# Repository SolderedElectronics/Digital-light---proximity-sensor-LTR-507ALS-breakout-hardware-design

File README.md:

# Digital light & proximity sensor LTR-507 breakout Hardware Design

## About the Product

|  |
| :----------------------------------------------------------: |
| [Buy Digital light & proximity sensor LTR-507 breakout](https://www.solde.red/333063) |

For very precise measurements of the amount of light, take this digital light sensor into account (ALS – Ambient Light Sensor). In addition, the LTR-507ALS also measures the proximity (PS – Proximity Sensor) of the object to the sensor. It sends all this data via I2C communication, which is easy to read via our Arduino library.

---

## Repository Contents

This repository contains all design files for Digital light & proximity sensor LTR-507 breakout, organized as follows:

- **`CAD` folder**: Contains KiCAD design files, including:
  - Schematics
  - PCB layout
  - Panel PCB layout
  - Source 3D files in Fusion360, if any
  - All files are sorted by version with a detailed change log.
- **`OUTPUTS` folder**: Includes all production-ready files, such as:
  - Bill of Materials (BOM) and interactive BOM (iBOM)
  - PDF versions of schematics
  - 3D `.step` file of the board
  - 3D-printable models
  - Gerber files for PCB manufacturing
  - Image of the pinout of the board
  - Product image
  - Compliance, legal and generic sales documents

Refer to the `Change Log` in the CAD folder for details about updates between versions.

---

## Learn More About the Product

Beyond the repository, explore the following resources:

### Soldered Verify

The **Soldered Verify** system ensures every board you purchase from Soldered is fully functional. It also provides access to exclusive test data for your product. To get started, find the unique Soldered Verify ID on your product's packaging and enter the ID on the [Soldered Verify page](https://soldered.com/verify/) to access test results and additional product details.

### Soldered Community

Soldered Community is your go-to place for technical support. Our engineers track and answer all questions posted there, and it’s a great space for the maker community. Get answers to your questions and solutions for your challenges at [Soldered Community](https://soldered.com/community).

### solde.red

solde.red is an ultimate URL shortener and information hub. Access it by typing solde.red/ followed by your product SKU, e.g., [solde.red/333000](https://solde.red/333000), to find getting-started guides, datasheets, open-source hardware and software files, certifications, images, pinouts, and more. Read more about the shortener [here](https://solde.red/info/).

---

## Contributing

Contributions are welcome! Here’s how you can get involved:

- Submit pull requests to enhance the design or fix issues.
- Report bugs or problems by opening an issue.

We encourage community collaboration to make this product even better.

---

## About Soldered

[Soldered for Makers](https://soldered.com) specializes in designing and manufacturing electronic products tailored for enthusiasts, ranging from hobbyists to professionals. Our portfolio includes electronic boards, sensors, and actuators that are widely utilized in fields such as microelectronics, mechatronics, robotics, programming, and IoT. Every product we offer is designed in-house and built upon open-source hardware and software platforms. Proudly certified and manufactured within the European Union, our catalog likely includes the product you need for your project.

We complement these products with comprehensive tutorials and manuals, product descriptions, schematics, programming codes, and project examples. Our round-the-clock [customer and technical support](https://soldered.com/community) is available for all our products, irrespective of the sales channel. Soldered’s success and services reflect our maker community’s unwavering [trust](https://www.trustpilot.com/review/soldered.com), for which we are deeply grateful. Join our community and create using Soldered products.

---

## License

All Soldered open-source hardware (OSH) is under The TAPR Open Hardware License. Read more in the LICENSE file located in this repository.

**Disclaimer:**

No warranty - all designs in this repository are distributed in the hope that they will be useful, but without any warranty. They are provided "AS IS", therefore without warranty of any kind, either expressed or implied. The entire quality and performance of what you do with the contents of this repository are your responsibility. In no event Soldered Electronics will be liable for your damages, or losses, including any general, special, incidental, or consequential damage arising out of the use or inability to use the contents of this repository. 

---

## Have fun!

Thank you for your support from your fellow makers at Soldered Electronics.

Happy Making!

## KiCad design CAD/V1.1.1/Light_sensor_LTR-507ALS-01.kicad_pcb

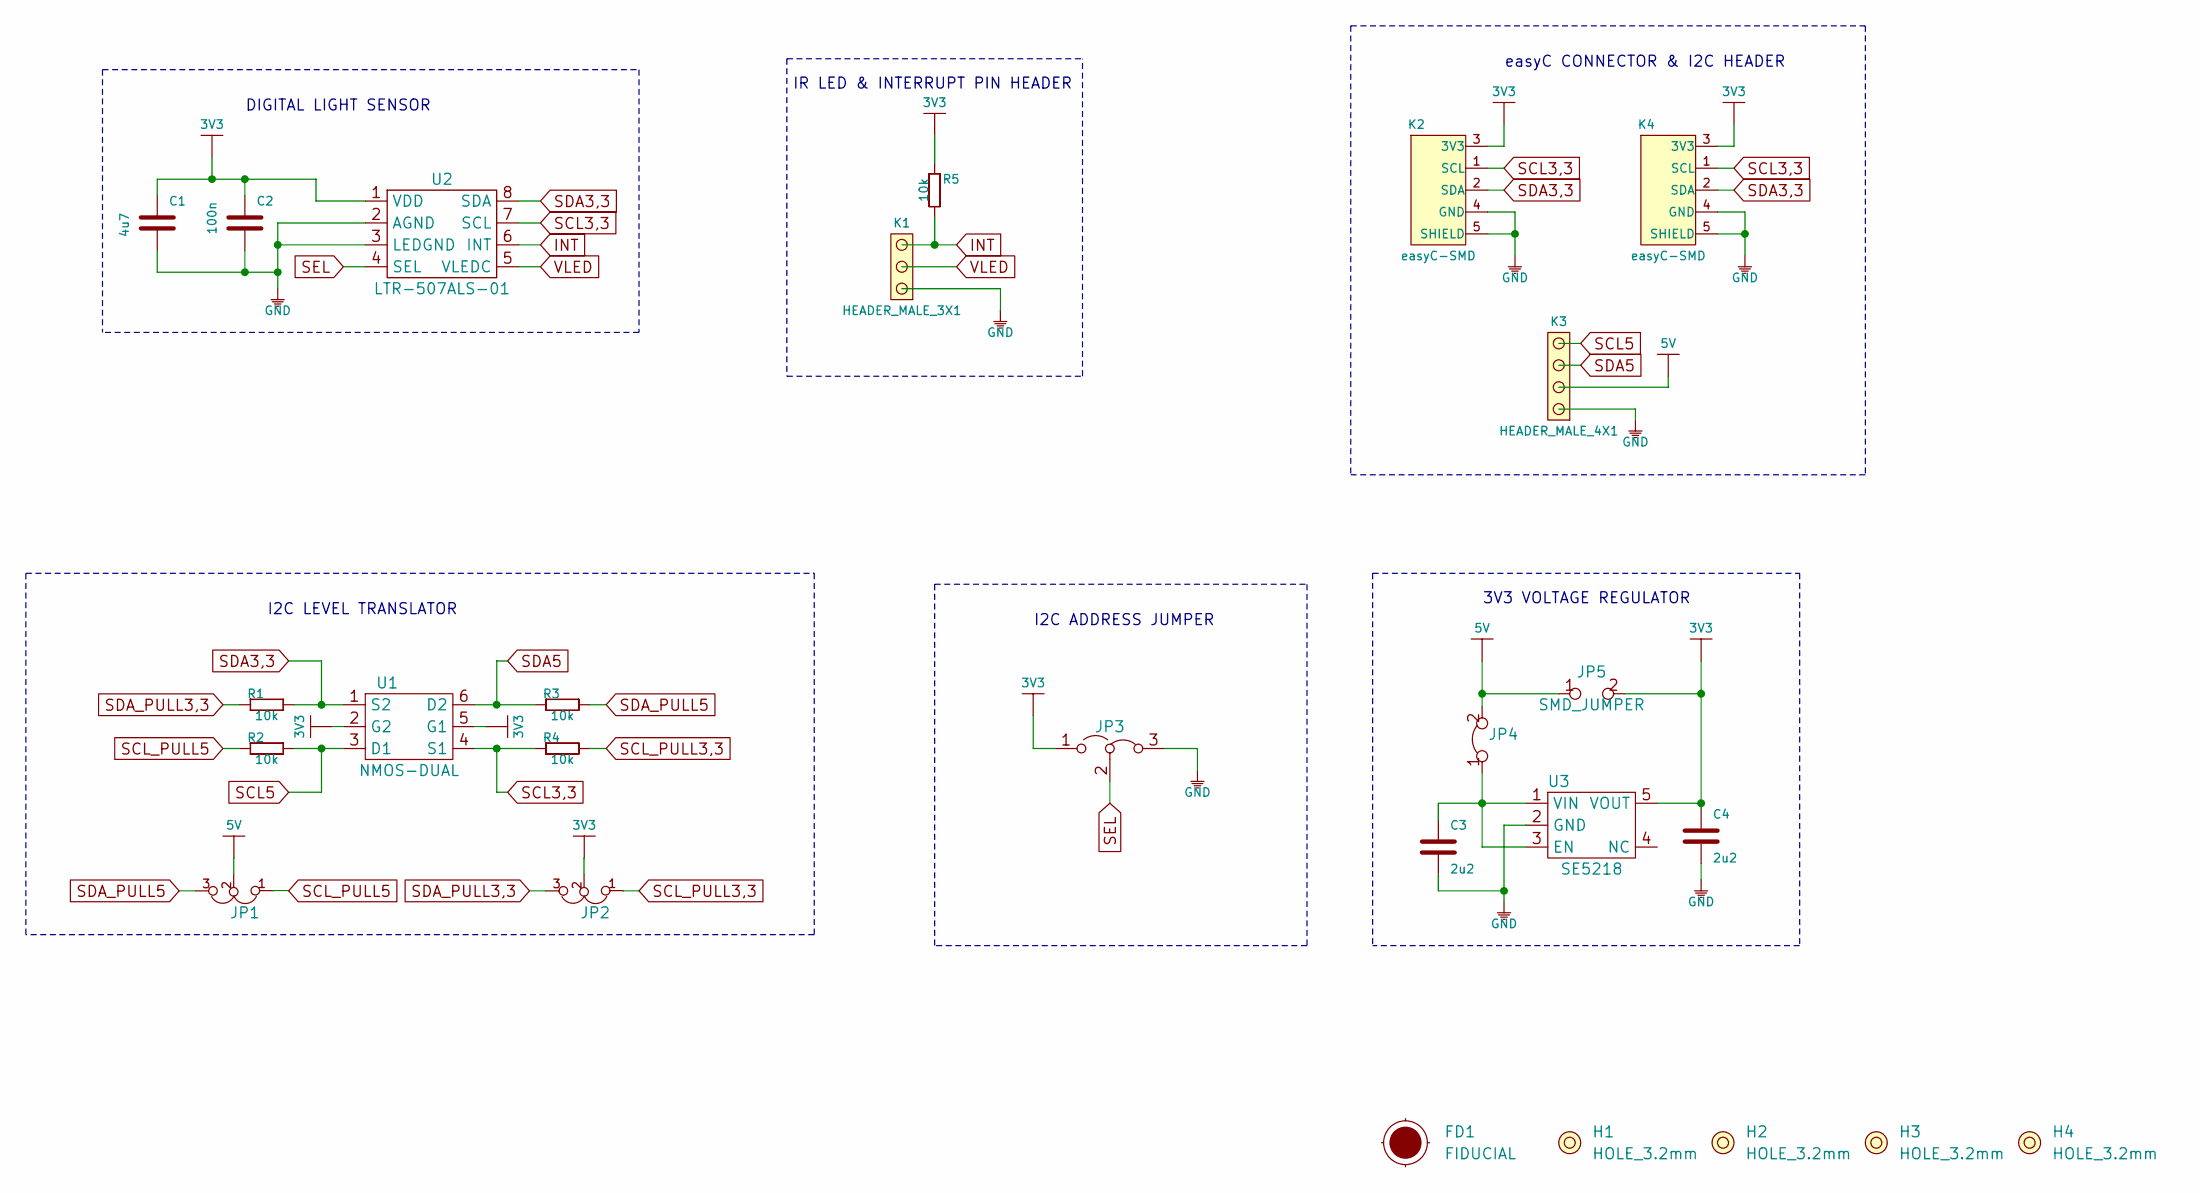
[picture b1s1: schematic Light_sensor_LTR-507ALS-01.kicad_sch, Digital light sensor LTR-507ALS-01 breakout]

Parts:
C1: 4u7; 0603C
C2: 100n; 0603C
C3, C4: 2u2; 0603C
FD1: FIDUCIAL; FIDUCIAL_23
H1, H2, H3, H4: HOLE_3.2mm
JP1, JP2: SMD_JUMPER_3_PAD_TRACE
JP3: JUMPER_3_RIGHT; SMD_JUMPER_3_PAD_CONNECTED_RIGHT
JP4: SMD-JUMPER-CONNECTED_TRACE_SLODERMASK
JP5: SMD_JUMPER
K1: HEADER_MALE_3X1
K2, K4: easyC-SMD; easyC-connector
K3: HEADER_MALE_4X1
R1, R2, R3, R4, R5: 10k; 0603R
U1: NMOS-DUAL; SOT-363
U2: LTR-507ALS-01
U3: SE5218; SOT-23-5

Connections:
3V3: C1.2, C2.2, C4.2, JP2.2, JP3.1 (A), JP5.2, K2.3 (3V3), K4.3 (3V3), R5.1, U1.2 (G2), U1.5 (G1), U2.1 (VDD), U3.5 (VOUT)
5V: JP1.2, JP4.2, JP5.1, K3.2
GND: C1.1, C2.1, C3.1, C4.1, JP3.3 (B), K1.1, K2.4 (GND), K2.5 (SHIELD), K3.1, K4.4 (GND), K4.5 (SHIELD), U2.2 (AGND), U2.3 (LEDGND), U3.2 (GND)
INT: K1.3, R5.2, U2.6 (INT)
unnamed: C3.2, JP4.1, U3.1 (VIN), U3.3 (EN)
SCL3,3: K2.1 (SCL), K4.1 (SCL), R4.1, U1.4 (S1), U2.7 (SCL)
SCL5: K3.4, R2.2, U1.3 (D1)
SCL_PULL3,3: JP2.1, R4.2
SCL_PULL5: JP1.1, R2.1
SDA3,3: K2.2 (SDA), K4.2 (SDA), R1.2, U1.1 (S2), U2.8 (SDA)
SDA5: K3.3, R3.1, U1.6 (D2)
SDA_PULL3,3: JP2.3, R1.1
SDA_PULL5: JP1.3, R3.2
SEL: JP3.2 (C), U2.4 (SEL)
VLED: K1.2, U2.5 (VLEDC)

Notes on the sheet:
IR LED & INTERRUPT PIN HEADER
easyC CONNECTOR & I2C HEADER
DIGITAL LIGHT SENSOR
I2C LEVEL TRANSLATOR
3V3 VOLTAGE REGULATOR
I2C ADDRESS JUMPER

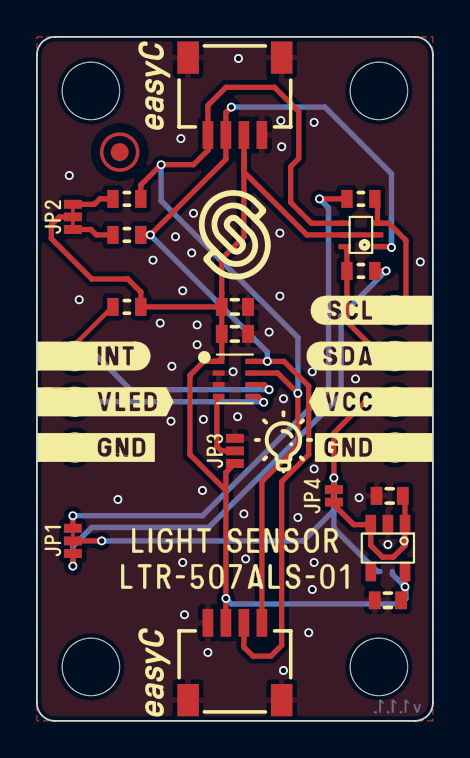
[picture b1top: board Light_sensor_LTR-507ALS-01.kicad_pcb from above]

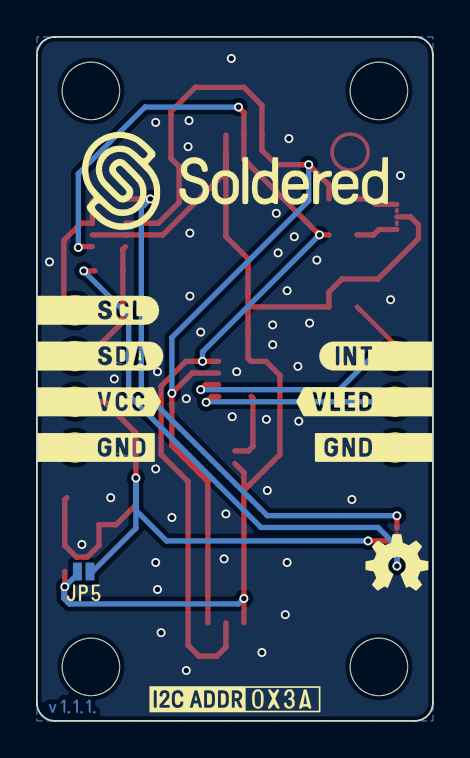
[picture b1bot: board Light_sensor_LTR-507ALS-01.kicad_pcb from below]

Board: 2 copper layers, 22.0 x 38.0 mm, 26 parts (3 on the bottom side), 15 nets.

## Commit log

2022-08-06 Updating open source files.
